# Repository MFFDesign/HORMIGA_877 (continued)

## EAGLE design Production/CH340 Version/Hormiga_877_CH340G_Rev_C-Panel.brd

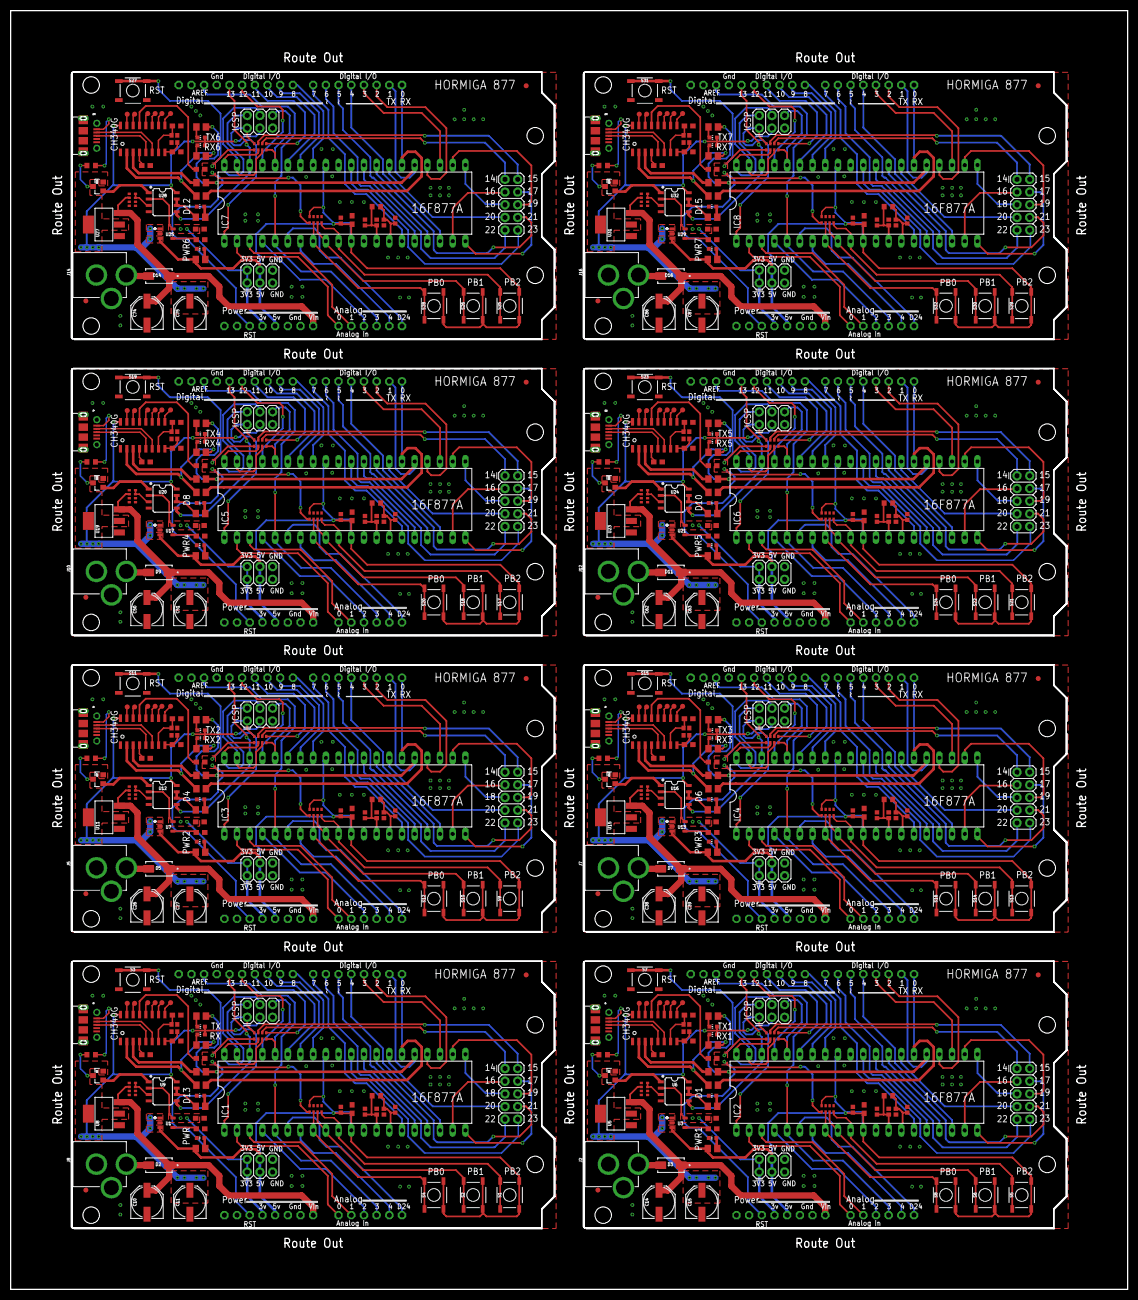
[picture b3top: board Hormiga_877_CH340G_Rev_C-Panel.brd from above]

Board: 2 copper layers, 223.6 x 256.0 mm, 432 parts (0 on the bottom side), 552 nets.

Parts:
C1, C7, C25, C37, C49, C61, C73, C85: 1.0uF; 0603
C2, C3, C18, C19, C30, C31, C42, C43, C54, C55, C66, C67, C78, C79, C90, C91: 15pF; 0402
C4, C20, C32, C44, C56, C68, C80, C92: 10nF; 0603
C5, C6, C21, C22, C33, C34, C45, C46, C57, C58, C69, C70, C81, C82, C93, C94: 22pF; C0603
C8, C23, C35, C47, C59, C71, C83, C95: 10uF; C0603
C9, C24, C36, C48, C60, C72, C84, C96: 0.1uF; C0603
C10, C11, C14, C15, C26, C27, C38, C39, C50, C51, C62, C63, C74, C75, C86, C87: 47uF; PANASONIC_D
C12, C16, C28, C40, C52, C64, C76, C88: 0.1uF; 0402
C13, C17, C29, C41, C53, C65, C77, C89: 15pF; C0603
CTS, CTS1, CTS2, CTS3, CTS4, CTS5, CTS6, CTS7: TEST-POINT3X4; PAD.03X.04
D1, D4, D6, D8, D10, D12, D13, D15: GRN; CHIP-LED0603
D2, D3, D5, D7, D9, D11, D14, D16: M7; DIOM505270X240
DCD, DCD1, DCD2, DCD3, DCD4, DCD5, DCD6, DCD7: TEST-POINT3X4; PAD.03X.04
DSR, DSR1, DSR2, DSR3, DSR4, DSR5, DSR6, DSR7: TEST-POINT3X4; PAD.03X.04
F1, F2, F3, F4, F5, F6, F7, F8, F9, F10, F11, F12, F13, F14, F15, F16: TPSQTP10R; TP10R
FUSE, FUSE1, FUSE2, FUSE3, FUSE4, FUSE5, FUSE6, FUSE7: FUSE0603; R0603
GPIO, GPIO1, GPIO2, GPIO3, GPIO4, GPIO5, GPIO6, GPIO7: 2X5
IC1, IC2, IC3, IC4, IC5, IC6, IC7, IC8: PIC18F4550_40; DIL40
ICSP, ICSP1, ICSP2, ICSP3, ICSP4, ICSP5, ICSP6, ICSP7: icsp; 2X3
J1, J3, J4, J6, J9, J11, J13, J15: 105017-0001; MOLEX_105017-0001
J2, J5, J7, J8, J10, J12, J14, J16: POWER_JACK; POWER_JACK_PTH
POWER, POWER1, POWER2, POWER3, POWER4, POWER5, POWER6, POWER7: POWER; 2X3
PWR, PWR1, PWR2, PWR3, PWR4, PWR5, PWR6, PWR7: GRN; CHIP-LED0603
Q1, Q4, Q7, Q10, Q13, Q16, Q19, Q22: FA-128_20MHz; FA-128
Q2, Q5, Q8, Q11, Q14, Q17, Q20, Q23: FA-128_12MHz; FA-128
Q3, Q6, Q9, Q12, Q15, Q18, Q21, Q24: SMD-MOSFET-P-CH-20V-2A(SOT-23); SOT-23
R1, R5, R6, R8, R12, R13, R15, R19, R20, R22, R26, R27, R29, R33, R34, R36, R40, R41, R43, R47, R48, R50, R54, R55: 330R; R0805
R2, R3, R9, R10, R16, R17, R23, R24, R30, R31, R37, R38, R44, R45, R51, R52: 1K; R0805
R4, R11, R18, R25, R32, R39, R46, R53: 1M; R0603
R7, R14, R21, R28, R35, R42, R49, R56: 470; R0805
RI, RI1, RI2, RI3, RI4, RI5, RI6, RI7: TEST-POINT3X4; PAD.03X.04
RN1, RN3, RN4, RN6, RN7, RN9, RN10, RN12, RN13, RN15, RN16, RN18, RN19, RN21, RN22, RN24: 10K; 0603-ARC
RN2, RN5, RN8, RN11, RN14, RN17, RN20, RN23: 100; 0603-ARC
RS1, RS2, RS3, RS4, RS5, RS6, RS7, RS232: TEST-POINT3X4; PAD.03X.04
RTS, RTS1, RTS2, RTS3, RTS4, RTS5, RTS6, RTS7: TEST-POINT3X4; PAD.03X.04
RX, RX1, RX2, RX3, RX4, RX5, RX6, RX7: GRN; CHIP-LED0603
S1, S2, S3, S4, S5, S6, S7, S8, S9, S10, S11, S12, S13, S14, S15, S16, S17, S18, S19, S20, S21, S22, S23, S24, S25, S26, S27, S28, S29, S30, S31, S32: MOMENTARY-SWITCH-SPST-SMD-5.2-REDUNDANT; TACTILE_SWITCH_SMD_5.2MM
TX, TX1, TX2, TX3, TX4, TX5, TX6, TX7: GRN; CHIP-LED0603
U1, U3, U7, U13, U17, U21, U25, U29: LP2985-33DBVR; SOT95P280X145-5N
U2, U4, U10, U14, U18, U22, U26, U30: ARDUINOR3-DIMENSION; ARDUINOR3
U5, U8, U11, U15, U19, U23, U27, U31: NCP1117; SOT223
U6, U9, U12, U16, U20, U24, U28, U32: LMV358; SO08
U$1, U$2, U$3, U$4, U$5, U$6, U$7, U$8: CH340G; SOIC16

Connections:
A0: IC1.2, U2.A0
A1: IC1.3, U2.A1
A2: IC1.4, U2.A2
A3: IC1.5, U2.A3, U2.AREF
A4: IC1.7, U2.A4
A5: IC2.2, U4.A0
A6: IC2.3, U4.A1
A7: IC2.4, U4.A2
A8: IC2.5, U4.A3, U4.AREF
A9: IC2.7, U4.A4
A10: IC3.2, U10.A0
A11: IC3.3, U10.A1
A12: IC3.4, U10.A2
A13: IC3.5, U10.A3, U10.AREF
A14: IC3.7, U10.A4
A15: IC4.2, U14.A0
A16: IC4.3, U14.A1
A17: IC4.4, U14.A2
A18: IC4.5, U14.A3, U14.AREF
A19: IC4.7, U14.A4
A20: IC5.2, U18.A0
A21: IC5.3, U18.A1
A22: IC5.4, U18.A2
A23: IC5.5, U18.A3, U18.AREF
A24: IC5.7, U18.A4
A25: IC6.2, U22.A0
A26: IC6.3, U22.A1
A27: IC6.4, U22.A2
A28: IC6.5, U22.A3, U22.AREF
A29: IC6.7, U22.A4
A30: IC7.2, U26.A0
A31: IC7.3, U26.A1
A32: IC7.4, U26.A2
A33: IC7.5, U26.A3, U26.AREF
A34: IC7.7, U26.A4
A35: IC8.2, U30.A0
A36: IC8.3, U30.A1
A37: IC8.4, U30.A2
A38: IC8.5, U30.A3, U30.AREF
A39: IC8.7, U30.A4
BUFF: R1.2, U9.6, U9.7
BUFF1: R8.2, U6.6, U6.7
BUFF2: R15.2, U12.6, U12.7
BUFF3: R22.2, U16.6, U16.7
BUFF4: R29.2, U20.6, U20.7
BUFF5: R36.2, U24.6, U24.7
BUFF6: R43.2, U28.6, U28.7
BUFF7: R50.2, U32.6, U32.7
BYPS: C4.1, U1.4
BYPS1: C20.1, U3.4
BYPS2: C32.1, U7.4
BYPS3: C44.1, U13.4
BYPS4: C56.1, U17.4
BYPS5: C68.1, U21.4
BYPS6: C80.1, U25.4
BYPS7: C92.1, U29.4
COMP: RN3.3, RN3.4, U9.3
COMP1: RN6.3, RN6.4, U6.3
COMP2: RN9.3, RN9.4, U12.3
COMP3: RN12.3, RN12.4, U16.3
COMP4: RN15.3, RN15.4, U20.3
COMP5: RN18.3, RN18.4, U24.3
COMP6: RN21.3, RN21.4, U28.3
COMP7: RN24.3, RN24.4, U32.3
CTS: CTS.P$1, U$1.9
CTS1: CTS1.P$1, U$2.9
CTS2: CTS2.P$1, U$3.9
CTS3: CTS3.P$1, U$4.9
CTS4: CTS4.P$1, U$5.9
CTS5: CTS5.P$1, U$6.9
CTS6: CTS6.P$1, U$7.9
CTS7: CTS7.P$1, U$8.9
D1: GPIO1.9, IC2.29
D2: IC1.24, U2.D2
D3: IC1.23, U2.D3
D4: IC1.18, U2.D4
D5: IC1.17, U2.D5
D6: IC1.16, U2.D6
D7: IC1.15, U2.D7
D8: IC1.33, U2.D8
D9: IC1.34, U2.D9
D10: IC1.35, U2.D10
D11: RN2.5, U2.D11
D12: IC1.37, U2.D12
D13: IC1.38, U2.D13, U9.5
D13LED: D13.A, R1.1
D13LED1: D1.A, R8.1
D13LED2: D4.A, R15.1
D13LED3: D6.A, R22.1
D13LED4: D8.A, R29.1
D13LED5: D10.A, R36.1
D13LED6: D12.A, R43.1
D13LED7: D15.A, R50.1
D14: GPIO.1, RN2.6
D15: GPIO.2, RN2.7
D16: GPIO.3, IC1.19
D17: GPIO.4, IC1.20
D18: GPIO.5, IC1.21
D19: GPIO.6, IC1.22
D20: GPIO.7, IC1.27
D21: GPIO.8, IC1.28
D22: GPIO.9, IC1.29
D23: GPIO.10, IC1.30
D24: IC1.6, U2.A5
D25: GPIO1.8, IC2.28
D26: GPIO1.7, IC2.27
D27: GPIO1.6, IC2.22
D28: GPIO1.5, IC2.21
D29: GPIO1.4, IC2.20
D30: GPIO1.3, IC2.19
D31: IC2.24, U4.D2
D32: IC2.23, U4.D3
D33: IC2.38, U4.D13, U6.5
D34: GPIO1.2, RN5.7
D35: IC2.18, U4.D4
D36: IC2.17, U4.D5
D37: IC2.16, U4.D6
D38: IC2.15, U4.D7
D39: IC2.33, U4.D8
D40: IC2.34, U4.D9
D41: IC2.35, U4.D10
D42: RN5.5, U4.D11
D43: IC2.37, U4.D12
D44: GPIO1.1, RN5.6
D45: GPIO1.10, IC2.30
D46: IC2.6, U4.A5
D47: GPIO2.9, IC3.29
D48: GPIO2.8, IC3.28
D49: GPIO2.7, IC3.27
D50: GPIO2.6, IC3.22
D51: GPIO2.5, IC3.21
D52: GPIO2.4, IC3.20
D53: GPIO2.3, IC3.19
D54: IC3.24, U10.D2
D55: IC3.23, U10.D3
D56: IC3.38, U10.D13, U12.5
D57: GPIO2.2, RN8.7
D58: IC3.18, U10.D4
D59: IC3.17, U10.D5
D60: IC3.16, U10.D6
D61: IC3.15, U10.D7
D62: IC3.33, U10.D8
D63: IC3.34, U10.D9
D64: IC3.35, U10.D10
D65: RN8.5, U10.D11
D66: IC3.37, U10.D12
D67: GPIO2.1, RN8.6
D68: GPIO2.10, IC3.30
D69: IC3.6, U10.A5
D70: GPIO3.9, IC4.29
D71: GPIO3.8, IC4.28
D72: GPIO3.7, IC4.27
D73: GPIO3.6, IC4.22
D74: GPIO3.5, IC4.21
D75: GPIO3.4, IC4.20
D76: GPIO3.3, IC4.19
D77: IC4.24, U14.D2
D78: IC4.23, U14.D3
D79: IC4.38, U14.D13, U16.5
D80: GPIO3.2, RN11.7
D81: IC4.18, U14.D4
D82: IC4.17, U14.D5
D83: IC4.16, U14.D6
D84: IC4.15, U14.D7
D85: IC4.33, U14.D8
D86: IC4.34, U14.D9
D87: IC4.35, U14.D10
D88: RN11.5, U14.D11
D89: IC4.37, U14.D12
D90: GPIO3.1, RN11.6
D91: GPIO3.10, IC4.30
D92: IC4.6, U14.A5
D93: GPIO4.9, IC5.29
D94: GPIO4.8, IC5.28
D95: GPIO4.7, IC5.27
D96: GPIO4.6, IC5.22
D97: GPIO4.5, IC5.21
D98: GPIO4.4, IC5.20
D99: GPIO4.3, IC5.19
D100: IC5.24, U18.D2
D101: IC5.23, U18.D3
D102: IC5.38, U18.D13, U20.5
D103: GPIO4.2, RN14.7
D104: IC5.18, U18.D4
D105: IC5.17, U18.D5
D106: IC5.16, U18.D6
D107: IC5.15, U18.D7
D108: IC5.33, U18.D8
D109: IC5.34, U18.D9
D110: IC5.35, U18.D10
D111: RN14.5, U18.D11
D112: IC5.37, U18.D12
D113: GPIO4.1, RN14.6
D114: GPIO4.10, IC5.30
D115: IC5.6, U18.A5
D116: GPIO5.9, IC6.29
D117: GPIO5.8, IC6.28
D118: GPIO5.7, IC6.27
D119: GPIO5.6, IC6.22
D120: GPIO5.5, IC6.21
D121: GPIO5.4, IC6.20
D122: GPIO5.3, IC6.19
D123: IC6.24, U22.D2
D124: IC6.23, U22.D3
D125: IC6.38, U22.D13, U24.5
D126: GPIO5.2, RN17.7
D127: IC6.18, U22.D4
D128: IC6.17, U22.D5
D129: IC6.16, U22.D6
D130: IC6.15, U22.D7
D131: IC6.33, U22.D8
D132: IC6.34, U22.D9
D133: IC6.35, U22.D10
D134: RN17.5, U22.D11
D135: IC6.37, U22.D12
D136: GPIO5.1, RN17.6
D137: GPIO5.10, IC6.30
D138: IC6.6, U22.A5
D139: GPIO6.9, IC7.29
D140: GPIO6.8, IC7.28
D141: GPIO6.7, IC7.27
D142: GPIO6.6, IC7.22
D143: GPIO6.5, IC7.21
D144: GPIO6.4, IC7.20
D145: GPIO6.3, IC7.19
D146: IC7.24, U26.D2
D147: IC7.23, U26.D3
D148: IC7.38, U26.D13, U28.5
D149: GPIO6.2, RN20.7
D150: IC7.18, U26.D4
D151: IC7.17, U26.D5
D152: IC7.16, U26.D6
D153: IC7.15, U26.D7
D154: IC7.33, U26.D8
D155: IC7.34, U26.D9
D156: IC7.35, U26.D10
D157: RN20.5, U26.D11
D158: IC7.37, U26.D12
D159: GPIO6.1, RN20.6
D160: GPIO6.10, IC7.30
D161: IC7.6, U26.A5
D162: GPIO7.9, IC8.29
D163: GPIO7.8, IC8.28
D164: GPIO7.7, IC8.27
D165: GPIO7.6, IC8.22
D166: GPIO7.5, IC8.21
D167: GPIO7.4, IC8.20
D168: GPIO7.3, IC8.19
D169: IC8.24, U30.D2
D170: IC8.23, U30.D3
D171: IC8.38, U30.D13, U32.5
D172: GPIO7.2, RN23.7
D173: IC8.18, U30.D4
D174: IC8.17, U30.D5
D175: IC8.16, U30.D6
D176: IC8.15, U30.D7
D177: IC8.33, U30.D8
D178: IC8.34, U30.D9
D179: IC8.35, U30.D10
D180: RN23.5, U30.D11
D181: IC8.37, U30.D12
D182: GPIO7.1, RN23.6
D183: GPIO7.10, IC8.30
D184: IC8.6, U30.A5
DATA1: R3.2, R6.1, U$1.2
DATA2: R2.2, U$1.3
DATA3: R9.2, U$2.3
DATA4: R10.2, R13.1, U$2.2
DATA5: R16.2, U$3.3
DATA6: R17.2, R20.1, U$3.2
DATA7: R23.2, U$4.3
DATA8: R24.2, R27.1, U$4.2
DATA9: R30.2, U$5.3
DATA10: R31.2, R34.1, U$5.2
DATA11: R37.2, U$6.3
DATA12: R38.2, R41.1, U$6.2
DATA13: R44.2, U$7.3
DATA14: R45.2, R48.1, U$7.2
DATA15: R51.2, U$8.3
DATA16: R52.2, R55.1, U$8.2
DATARX: IC1.26, R3.1, U2.D0
DATARX1: IC2.26, R10.1, U4.D0
DATARX2: IC3.26, R17.1, U10.D0
DATARX3: IC4.26, R24.1, U14.D0
DATARX4: IC5.26, R31.1, U18.D0
DATARX5: IC6.26, R38.1, U22.D0
DATARX6: IC7.26, R45.1, U26.D0
DATARX7: IC8.26, R52.1, U30.D0
DATATX: IC1.25, R2.1, R5.1, U2.D1
DATATX1: IC2.25, R9.1, R12.1, U4.D1
DATATX2: IC3.25, R16.1, R19.1, U10.D1
DATATX3: IC4.25, R23.1, R26.1, U14.D1
DATATX4: IC5.25, R30.1, R33.1, U18.D1
DATATX5: IC6.25, R37.1, R40.1, U22.D1
DATATX6: IC7.25, R44.1, R47.1, U26.D1
DATATX7: IC8.25, R51.1, R54.1, U30.D1
DCD: DCD.P$1, U$1.12
DCD1: DCD1.P$1, U$2.12
DCD2: DCD2.P$1, U$3.12
DCD3: DCD3.P$1, U$4.12
DCD4: DCD4.P$1, U$5.12
DCD5: DCD5.P$1, U$6.12
DCD6: DCD6.P$1, U$7.12
DCD7: DCD7.P$1, U$8.12
DSR: DSR.P$1, U$1.10
DSR1: DSR1.P$1, U$2.10
DSR2: DSR2.P$1, U$3.10
DSR3: DSR3.P$1, U$4.10
DSR4: DSR4.P$1, U$5.10
DSR5: DSR5.P$1, U$6.10
DSR6: DSR6.P$1, U$7.10
DSR7: DSR7.P$1, U$8.10
DTR: C9.1, U$1.13
DTR1: C24.1, U$2.13
DTR2: C36.1, U$3.13
DTR3: C48.1, U$4.13
DTR4: C60.1, U$5.13
DTR5: C72.1, U$6.13
DTR6: C84.1, U$7.13
DTR7: C96.1, U$8.13
FUSE: FUSE.1, J3.1
FUSE1: FUSE1.1, J1.1
FUSE2: FUSE2.1, J4.1
FUSE3: FUSE3.1, J6.1
FUSE4: FUSE4.1, J9.1
FUSE5: FUSE5.1, J11.1
FUSE6: FUSE6.1, J13.1
FUSE7: FUSE7.1, J15.1
GATE_CMD: Q3.1, U9.1
GATE_CMD1: Q6.1, U6.1
GATE_CMD2: Q9.1, U12.1
GATE_CMD3: Q12.1, U16.1
GATE_CMD4: Q15.1, U20.1
GATE_CMD5: Q18.1, U24.1
GATE_CMD6: Q21.1, U28.1
GATE_CMD7: Q24.1, U32.1
GND: C1.2, C2.2, C3.2, C4.2, C5.2, C6.2, C8.2, C10.-, C11.-, C12.2, C13.2, D13.C, IC1.12, IC1.31, ICSP.5, J3.5, J8.GND, J8.GNDBREAK, POWER.5, POWER.6, PWR.C, Q1.2, Q1.4, Q2.2, Q2.4, RN1.5, RN1.6, RN1.7, RN3.5, S3.3, S3.4, U1.2, U2.GND, U2.GND1, U2.GND2, U8.1, U9.4, U$1.1
GND1: C7.2, C14.-, C15.-, C16.2, C17.2, C18.2, C19.2, C20.2, C21.2, C22.2, C23.2, D1.C, IC2.12, IC2.31, ICSP1.5, J1.5, J2.GND, J2.GNDBREAK, POWER1.5, POWER1.6, PWR1.C, Q4.2, Q4.4, Q5.2, Q5.4, RN4.5, RN4.6, RN4.7, RN6.5, S7.3, S7.4, U3.2, U4.GND, U4.GND1, U4.GND2, U5.1, U6.4, U$2.1
GND2: C25.2, C26.-, C27.-, C28.2, C29.2, C30.2, C31.2, C32.2, C33.2, C34.2, C35.2, D4.C, IC3.12, IC3.31, ICSP2.5, J4.5, J5.GND, J5.GNDBREAK, POWER2.5, POWER2.6, PWR2.C, Q7.2, Q7.4, Q8.2, Q8.4, RN7.5, RN7.6, RN7.7, RN9.5, S11.3, S11.4, U7.2, U10.GND, U10.GND1, U10.GND2, U11.1, U12.4, U$3.1
GND3: C37.2, C38.-, C39.-, C40.2, C41.2, C42.2, C43.2, C44.2, C45.2, C46.2, C47.2, D6.C, IC4.12, IC4.31, ICSP3.5, J6.5, J7.GND, J7.GNDBREAK, POWER3.5, POWER3.6, PWR3.C, Q10.2, Q10.4, Q11.2, Q11.4, RN10.5, RN10.6, RN10.7, RN12.5, S15.3, S15.4, U13.2, U14.GND, U14.GND1, U14.GND2, U15.1, U16.4, U$4.1
GND4: C49.2, C50.-, C51.-, C52.2, C53.2, C54.2, C55.2, C56.2, C57.2, C58.2, C59.2, D8.C, IC5.12, IC5.31, ICSP4.5, J9.5, J10.GND, J10.GNDBREAK, POWER4.5, POWER4.6, PWR4.C, Q13.2, Q13.4, Q14.2, Q14.4, RN13.5, RN13.6, RN13.7, RN15.5, S19.3, S19.4, U17.2, U18.GND, U18.GND1, U18.GND2, U19.1, U20.4, U$5.1
GND5: C61.2, C62.-, C63.-, C64.2, C65.2, C66.2, C67.2, C68.2, C69.2, C70.2, C71.2, D10.C, IC6.12, IC6.31, ICSP5.5, J11.5, J12.GND, J12.GNDBREAK, POWER5.5, POWER5.6, PWR5.C, Q16.2, Q16.4, Q17.2, Q17.4, RN16.5, RN16.6, RN16.7, RN18.5, S23.3, S23.4, U21.2, U22.GND, U22.GND1, U22.GND2, U23.1, U24.4, U$6.1
GND6: C73.2, C74.-, C75.-, C76.2, C77.2, C78.2, C79.2, C80.2, C81.2, C82.2, C83.2, D12.C, IC7.12, IC7.31, ICSP6.5, J13.5, J14.GND, J14.GNDBREAK, POWER6.5, POWER6.6, PWR6.C, Q19.2, Q19.4, Q20.2, Q20.4, RN19.5, RN19.6, RN19.7, RN21.5, S27.3, S27.4, U25.2, U26.GND, U26.GND1, U26.GND2, U27.1, U28.4, U$7.1
GND7: C85.2, C86.-, C87.-, C88.2, C89.2, C90.2, C91.2, C92.2, C93.2, C94.2, C95.2, D15.C, IC8.12, IC8.31, ICSP7.5, J15.5, J16.GND, J16.GNDBREAK, POWER7.5, POWER7.6, PWR7.C, Q22.2, Q22.4, Q23.2, Q23.4, RN22.5, RN22.6, RN22.7, RN24.5, S31.3, S31.4, U29.2, U30.GND, U30.GND1, U30.GND2, U31.1, U32.4, U$8.1
LEDRX: R6.2, RX.C
LEDRX1: R13.2, RX1.C
LEDRX2: R20.2, RX2.C
LEDRX3: R27.2, RX3.C
LEDRX4: R34.2, RX4.C
LEDRX5: R41.2, RX5.C
LEDRX6: R48.2, RX6.C
LEDRX7: R55.2, RX7.C
LEDTX: R5.2, TX.C
LEDTX1: R12.2, TX1.C
LEDTX2: R19.2, TX2.C
LEDTX3: R26.2, TX3.C
LEDTX4: R33.2, TX4.C
LEDTX5: R40.2, TX5.C
LEDTX6: R47.2, TX6.C
LEDTX7: R54.2, TX7.C
MCLR: IC1.1, ICSP.1, RN2.8
MCLR1: IC2.1, ICSP1.1, RN5.8
MCLR2: IC3.1, ICSP2.1, RN8.8
MCLR3: IC4.1, ICSP3.1, RN11.8
MCLR4: IC5.1, ICSP4.1, RN14.8
MCLR5: IC6.1, ICSP5.1, RN17.8
MCLR6: IC7.1, ICSP6.1, RN20.8
MCLR7: IC8.1, ICSP7.1, RN23.8
ONLED: PWR.A, R7.1
ONLED1: PWR1.A, R14.1
ONLED2: PWR2.A, R21.1
ONLED3: PWR3.A, R28.1
ONLED4: PWR4.A, R35.1
ONLED5: PWR5.A, R42.1
ONLED6: PWR6.A, R49.1
ONLED7: PWR7.A, R56.1
OSC1: C2.1, IC1.13, Q1.1, R4.1
OSC2: C3.1, IC1.14, Q1.3, R4.2
OSC3: C18.1, IC2.13, Q4.1, R11.1
OSC4: C19.1, IC2.14, Q4.3, R11.2
OSC5: C30.1, IC3.13, Q7.1, R18.1
OSC6: C31.1, IC3.14, Q7.3, R18.2
OSC7: C42.1, IC4.13, Q10.1, R25.1
OSC8: C43.1, IC4.14, Q10.3, R25.2
OSC9: C54.1, IC5.13, Q13.1, R32.1
OSC10: C55.1, IC5.14, Q13.3, R32.2
OSC11: C66.1, IC6.13, Q16.1, R39.1
OSC12: C67.1, IC6.14, Q16.3, R39.2
OSC13: C78.1, IC7.13, Q19.1, R46.1
OSC14: C79.1, IC7.14, Q19.3, R46.2
OSC15: C90.1, IC8.13, Q22.1, R53.1
OSC16: C91.1, IC8.14, Q22.3, R53.2
PGC: IC1.39, ICSP.4, RN2.3
PGC1: IC2.39, ICSP1.4, RN5.3
PGC2: IC3.39, ICSP2.4, RN8.3
PGC3: IC4.39, ICSP3.4, RN11.3
PGC4: IC5.39, ICSP4.4, RN14.3
PGC5: IC6.39, ICSP5.4, RN17.3
PGC6: IC7.39, ICSP6.4, RN20.3
PGC7: IC8.39, ICSP7.4, RN23.3
PGD: IC1.40, ICSP.2, RN2.2
PGD1: IC2.40, ICSP1.2, RN5.2
PGD2: IC3.40, ICSP2.2, RN8.2
PGD3: IC4.40, ICSP3.2, RN11.2
PGD4: IC5.40, ICSP4.2, RN14.2
PGD5: IC6.40, ICSP5.2, RN17.2
PGD6: IC7.40, ICSP6.2, RN20.2
PGD7: IC8.40, ICSP7.2, RN23.2
PGM: IC1.36, ICSP.6, RN2.4
PGM1: IC2.36, ICSP1.6, RN5.4
PGM2: IC3.36, ICSP2.6, RN8.4
PGM3: IC4.36, ICSP3.6, RN11.4
PGM4: IC5.36, ICSP4.6, RN14.4
PGM5: IC6.36, ICSP5.6, RN17.4
PGM6: IC7.36, ICSP6.6, RN20.4
PGM7: IC8.36, ICSP7.6, RN23.4
PWRIN: D2.A, J8.PWR
PWRIN1: D3.A, J2.PWR
PWRIN2: D5.A, J5.PWR
PWRIN3: D7.A, J7.PWR
PWRIN4: D9.A, J10.PWR
PWRIN5: D11.A, J12.PWR
PWRIN6: D14.A, J14.PWR
PWRIN7: D16.A, J16.PWR
RE0: IC1.8, RN1.2, S4.1, S4.2
RE1: IC1.9, RN1.3, S2.1, S2.2
RE2: IC1.10, RN1.4, S1.1, S1.2
RE3: IC2.8, RN4.2, S8.1, S8.2
RE4: IC2.9, RN4.3, S6.1, S6.2
RE5: IC2.10, RN4.4, S5.1, S5.2
RE6: IC3.8, RN7.2, S12.1, S12.2
RE7: IC3.9, RN7.3, S10.1, S10.2
RE8: IC3.10, RN7.4, S9.1, S9.2
RE9: IC4.8, RN10.2, S16.1, S16.2
RE10: IC4.9, RN10.3, S14.1, S14.2
RE11: IC4.10, RN10.4, S13.1, S13.2
RE12: IC5.8, RN13.2, S20.1, S20.2
RE13: IC5.9, RN13.3, S18.1, S18.2
RE14: IC5.10, RN13.4, S17.1, S17.2
RE15: IC6.8, RN16.2, S24.1, S24.2
RE16: IC6.9, RN16.3, S22.1, S22.2
RE17: IC6.10, RN16.4, S21.1, S21.2
RE18: IC7.8, RN19.2, S28.1, S28.2
RE19: IC7.9, RN19.3, S26.1, S26.2
RE20: IC7.10, RN19.4, S25.1, S25.2
RE21: IC8.8, RN22.2, S32.1, S32.2
RE22: IC8.9, RN22.3, S30.1, S30.2
RE23: IC8.10, RN22.4, S29.1, S29.2
RESET: C9.2, RN1.1, RN2.1, S3.1, S3.2, U2.RESET
RESET1: C24.2, RN4.1, RN5.1, S7.1, S7.2, U4.RESET
RESET2: C36.2, RN7.1, RN8.1, S11.1, S11.2, U10.RESET
RESET3: C48.2, RN10.1, RN11.1, S15.1, S15.2, U14.RESET
RESET4: C60.2, RN13.1, RN14.1, S19.1, S19.2, U18.RESET
RESET5: C72.2, RN16.1, RN17.1, S23.1, S23.2, U22.RESET
RESET6: C84.2, RN19.1, RN20.1, S27.1, S27.2, U26.RESET
RESET7: C96.2, RN22.1, RN23.1, S31.1, S31.2, U30.RESET
RI: RI.P$1, U$1.11
RI1: RI1.P$1, U$2.11
RI2: RI2.P$1, U$3.11
RI3: RI3.P$1, U$4.11
RI4: RI4.P$1, U$5.11
RI5: RI5.P$1, U$6.11
RI6: RI6.P$1, U$7.11
RI7: RI7.P$1, U$8.11
RS1: RS1.P$1, U$2.15
RS2: RS2.P$1, U$3.15
RS3: RS3.P$1, U$4.15
RS4: RS4.P$1, U$5.15
RS5: RS5.P$1, U$6.15
RS6: RS6.P$1, U$7.15
RS7: RS7.P$1, U$8.15
RS232: RS232.P$1, U$1.15
RTS: RTS.P$1, U$1.14
RTS1: RTS1.P$1, U$2.14
RTS2: RTS2.P$1, U$3.14
RTS3: RTS3.P$1, U$4.14
RTS4: RTS4.P$1, U$5.14
RTS5: RTS5.P$1, U$6.14
RTS6: RTS6.P$1, U$7.14
RTS7: RTS7.P$1, U$8.14
USB_N: J3.2, U$1.6
USB_N1: J1.2, U$2.6
USB_N2: J4.2, U$3.6
USB_N3: J6.2, U$4.6
USB_N4: J9.2, U$5.6
USB_N5: J11.2, U$6.6
USB_N6: J13.2, U$7.6
USB_N7: J15.2, U$8.6
USB_P: J3.3, U$1.5
USB_P1: J1.3, U$2.5
USB_P2: J4.3, U$3.5
USB_P3: J6.3, U$4.5
USB_P4: J9.3, U$5.5
USB_P5: J11.3, U$6.5
USB_P6: J13.3, U$7.5
USB_P7: J15.3, U$8.5
V1: C17.1, U$2.4
V2: C29.1, U$3.4
V3: C13.1, U$1.4
V4: C41.1, U$4.4
V5: C53.1, U$5.4
V5VUSB: FUSE.2, Q3.3
V5VUSB1: FUSE1.2, Q6.3
V5VUSB2: FUSE2.2, Q9.3
V5VUSB3: FUSE3.2, Q12.3
V5VUSB4: FUSE4.2, Q15.3
V5VUSB5: FUSE5.2, Q18.3
V5VUSB6: FUSE6.2, Q21.3
V5VUSB7: FUSE7.2, Q24.3
V6: C65.1, U$6.4
V7: C77.1, U$7.4
V8: C89.1, U$8.4
VCC_1: C7.1, POWER1.1, POWER1.2, U3.5, U4.3V, U6.2
VCC_2: C1.1, POWER.1, POWER.2, U1.5, U2.3V, U9.2
VCC_3: C25.1, POWER2.1, POWER2.2, U7.5, U10.3V, U12.2
VCC_4: C37.1, POWER3.1, POWER3.2, U13.5, U14.3V, U16.2
VCC_5: C49.1, POWER4.1, POWER4.2, U17.5, U18.3V, U20.2
VCC_6: C61.1, POWER5.1, POWER5.2, U21.5, U22.3V, U24.2
VCC_7: C73.1, POWER6.1, POWER6.2, U25.5, U26.3V, U28.2
VCC_8: C85.1, POWER7.1, POWER7.2, U29.5, U30.3V, U32.2
VDD: C8.1, C11.+, C12.1, IC1.11, IC1.32, ICSP.3, POWER.3, POWER.4, Q3.2, R7.2, RN1.8, RX.A, S1.3, S1.4, S2.3, S2.4, S4.3, S4.4, TX.A, U1.1, U1.3, U2.5V, U8.2, U8.4, U9.8, U$1.16
VDD1: C15.+, C16.1, C23.1, IC2.11, IC2.32, ICSP1.3, POWER1.3, POWER1.4, Q6.2, R14.2, RN4.8, RX1.A, S5.3, S5.4, S6.3, S6.4, S8.3, S8.4, TX1.A, U3.1, U3.3, U4.5V, U5.2, U5.4, U6.8, U$2.16
VDD2: C27.+, C28.1, C35.1, IC3.11, IC3.32, ICSP2.3, POWER2.3, POWER2.4, Q9.2, R21.2, RN7.8, RX2.A, S9.3, S9.4, S10.3, S10.4, S12.3, S12.4, TX2.A, U7.1, U7.3, U10.5V, U11.2, U11.4, U12.8, U$3.16
VDD3: C39.+, C40.1, C47.1, IC4.11, IC4.32, ICSP3.3, POWER3.3, POWER3.4, Q12.2, R28.2, RN10.8, RX3.A, S13.3, S13.4, S14.3, S14.4, S16.3, S16.4, TX3.A, U13.1, U13.3, U14.5V, U15.2, U15.4, U16.8, U$4.16
VDD4: C51.+, C52.1, C59.1, IC5.11, IC5.32, ICSP4.3, POWER4.3, POWER4.4, Q15.2, R35.2, RN13.8, RX4.A, S17.3, S17.4, S18.3, S18.4, S20.3, S20.4, TX4.A, U17.1, U17.3, U18.5V, U19.2, U19.4, U20.8, U$5.16
VDD5: C63.+, C64.1, C71.1, IC6.11, IC6.32, ICSP5.3, POWER5.3, POWER5.4, Q18.2, R42.2, RN16.8, RX5.A, S21.3, S21.4, S22.3, S22.4, S24.3, S24.4, TX5.A, U21.1, U21.3, U22.5V, U23.2, U23.4, U24.8, U$6.16
VDD6: C75.+, C76.1, C83.1, IC7.11, IC7.32, ICSP6.3, POWER6.3, POWER6.4, Q21.2, R49.2, RN19.8, RX6.A, S25.3, S25.4, S26.3, S26.4, S28.3, S28.4, TX6.A, U25.1, U25.3, U26.5V, U27.2, U27.4, U28.8, U$7.16
VDD7: C87.+, C88.1, C95.1, IC8.11, IC8.32, ICSP7.3, POWER7.3, POWER7.4, Q24.2, R56.2, RN22.8, RX7.A, S29.3, S29.4, S30.3, S30.4, S32.3, S32.4, TX7.A, U29.1, U29.3, U30.5V, U31.2, U31.4, U32.8, U$8.16
VIN: C10.+, D2.C, RN3.6, U2.VIN, U8.3
VIN1: C14.+, D3.C, RN6.6, U4.VIN, U5.3
VIN2: C26.+, D5.C, RN9.6, U10.VIN, U11.3
VIN3: C38.+, D7.C, RN12.6, U14.VIN, U15.3
VIN4: C50.+, D9.C, RN15.6, U18.VIN, U19.3
VIN5: C62.+, D11.C, RN18.6, U22.VIN, U23.3
VIN6: C74.+, D14.C, RN21.6, U26.VIN, U27.3
VIN7: C86.+, D16.C, RN24.6, U30.VIN, U31.3
XI: C5.1, Q2.1, U$1.7
XI1: C21.1, Q5.1, U$2.7
XI2: C33.1, Q8.1, U$3.7
XI3: C45.1, Q11.1, U$4.7
XI4: C57.1, Q14.1, U$5.7
XI5: C69.1, Q17.1, U$6.7
XI6: C81.1, Q20.1, U$7.7
XI7: C93.1, Q23.1, U$8.7
XO: C6.1, Q2.3, U$1.8
XO1: C22.1, Q5.3, U$2.8
XO2: C34.1, Q8.3, U$3.8
XO3: C46.1, Q11.3, U$4.8
XO4: C58.1, Q14.3, U$5.8
XO5: C70.1, Q17.3, U$6.8
XO6: C82.1, Q20.3, U$7.8
XO7: C94.1, Q23.3, U$8.8

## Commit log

2019-10-28 Add files via upload
    Funcion "SerialBegin()" modificada para todos las Velocidades de Conexion Serial; Probados: 9600 bps.
2020-05-29 Add files via upload
    Revisión del código fuente y optimizaciones en el código.
2020-05-29 Inforgrafia de la Hormiga 877
2020-06-12 Revisión menor del proyecto de Hormiga 877
2020-06-14 Hormiga 877 Usando PIC C v4.104
    Conjunto de procedimientos para operar la placa Hormiga 877 mediante el compilador PIC C v4.104, versión en fase alpha, usalo bajo tu responsabilidad.
2020-06-16 Se corrigen errores al compilar el codigo
2020-06-18 Hormiga 877 Black Edition
    Proyecto usado para el manejo de la Hormiga 877 "Black Edition"; contiene las abstracciones y procedimientos para operar correctamente las terminales de la hormiga 877.
2020-06-18 Ejemplos de uso Hormiga 877
    ejemplos de codigo de como usar la placa Hormiga 877 para el manejo de diversos perifericos y módulos internos del PIC16F877A, tales como el convertidor analogico digital, el modulo Capture Compare P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
2020-06-18 Hormiga 877 Black Edition
    Distribución de Pines para la Hormiga 877 Black Edition, distinguiéndose principalmente, por el color que la placa de circuito impreso posee, además de la asignación de terminales de entrada y salida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
2020-06-20 Ejemplos Hormiga 877
2020-06-20 PBRead Added
    PBRead agregado y modificado para invertir señal.
2020-06-25 encender un LED con boton
2020-06-25 Ejemplo Maquina de Estados.
    Ejemplo de Maquina de Estados Tipo Moore para encender y apagar un diodo LED.
2020-06-26 Archivos para PIC C V4
2020-06-26 analogWrite Modificado
    Se corrigen registros para el correcto funcionamiento del modulo de salida analogica, asi como archivos de inicializacion de las salidas analogicas PWM.
2020-06-26 Simulacion Proteus v7.7
2020-06-27 Ejemplo de uso de Máquinas de Estados
    Ejemplo de cómo Encender y apagar un diodo LED, usando un solo botón, mediante la implementación de una máquina de estados.
2020-06-27 Ejemplo Maquina de Estados.
    Encender y apagar un diodo LED con un solo boton empleando una maquina de estados.
2020-06-27 Semaforo_Maquina_Estados
    Implementación de un Semaforo con Maquina de Estados.
2020-06-29 Maquina_Estados
2020-08-13 Cambiar frecuencia de PWM dinámicamente
2020-08-15 Contador_Pastillas
2020-08-15 Contador_pastillas header
2020-08-24 Generador de Funciones seno
2020-08-28 Maquina de Estados con LCD
2020-08-28 Uso de punteros para manejo de variables con LCD
2020-08-28 Uso de punteros con arreglos de datos
2020-08-30 uso de punteros en funciones
2020-09-12 Con Funciones corregidas del AD9850
2020-09-12 Funciones y Empleo de AD9850 Agregadas
2020-09-29 Uso sencillo de Modulación de Ancho de Pulso.
2021-07-11 Parallel Transmition Shift register Data chain
    "high speed data transmision, using Data Matrix, pointers and functions.
2021-11-11 Revised Squematic
2022-03-15 Uso de Interrupcion Externa en D8 (RB0)
    Es necesario declarar las funciones prototipo el archivo a exepcion del setup() y loop()
2022-03-15 Interrupcion Externa en D8 (RB0)
    es necesario declarar los prototipos de las funciones a exepcion de setup() y loop()
2022-03-15 Int en RB0/D8
    es necesario declarar los prototipos de las funciones a exepcion de setup() y loop()
2022-03-16 Selector de Practicas con Menus
    Se usa Maquina de estados para poder incorporar multiples objetos en un Menu
2022-03-27 Create Tacometro.c
    Tacometro de Medicion en Hertz y RPMs, verificado con osciloscopio el margen de error esta en +/- 3Hz
2022-03-27 Proyecto Tacometro
    Tiene Salida Serial Indicando la frecuencia en Hertz y en RPMs
2022-03-29 Delete HormigaLoader.exe
    dar credito a autor
2022-03-29 Tiny bootloader
2022-03-30 Control de Atenuacion Cargas AC
    Programa de Ejemplo para demostras un Dimmer de corriente alterna
2022-08-15 Medir Distancia con Sensor Ultrasonico en mm
2023-02-02 Port Update
2023-02-02 Se actualiza libreria Hormiga877
2023-02-02 Actualizacion Hormiga877
    se actualiza la libreria de Hormiga 877
2023-02-02 Actualizacion de Librerias de Hormiga877
2023-02-02 Actualizacion Mayor de Librerias
2023-02-03 Se Actualiza Libreria Stepper.c
2023-02-03 Prueba1
2023-02-03 Se edita Tonche Test Branch
2023-02-03 Agrego Tiempo en LCD
2023-02-03 Se configura el tiempo de muestreo
2023-02-03 Se agrega algoritmo PID
2023-02-07 Configuracion de PID
2023-02-07 Se corrige PID
2023-02-07 Se agrega la interpolacion lineal
2023-02-07 Se corrige llibreria PID
2023-02-08 Se agregan funciones de retardo por HW
2023-02-20 Se agrega SetOutputRanges
2023-02-20 Se Agregan Librerias prexistentes
2023-12-04 Archivos CAD
2023-12-04 Organizacion e Inicializacion
    Se agregan archivo y se organizan
2023-12-04 Se agrega version Funcional de FTDI
